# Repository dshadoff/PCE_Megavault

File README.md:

# Multi-Backup Megavault

This is code to run on a 4-megabit Flash memory (SST39SF040), which allows the
save and load of PC Engine backup memory to the flash memory on the cartridge.

The current version allows up to 32 backup memory slots to be saved along with
date infromation and a name/label for the save data.  There is substantially
more space to save information (both data and meta-data), with the possibility
of roughly 100 save areas plus paragraph-length descriptive information (however,
this would require some rethinking of the user interface).

As the NOR Flash is rated for 100 years and 100,000 write cycles, there is no
concern about lifetime under the usage in this application.  The techniques used
in this application can be used for other similar applications as well:
- usage counting
- save data within a cartridge, not relying on CDROM backup memory
- "protection" against usage on unauthorized hardware (check chip identification)

Note that as the special write commands involve specific read/write patterns at
specific addresses, the flash commands cannot be run from the flash memory itself; 
instead, these sepcific sequences have been relocated to execute from user SRAM.

This is prototype software, and as such has been minimally tested.
Use at your own risk.

Also in theis repository is the board layout information for EAGLE, in order
to get these PC board fabricated.

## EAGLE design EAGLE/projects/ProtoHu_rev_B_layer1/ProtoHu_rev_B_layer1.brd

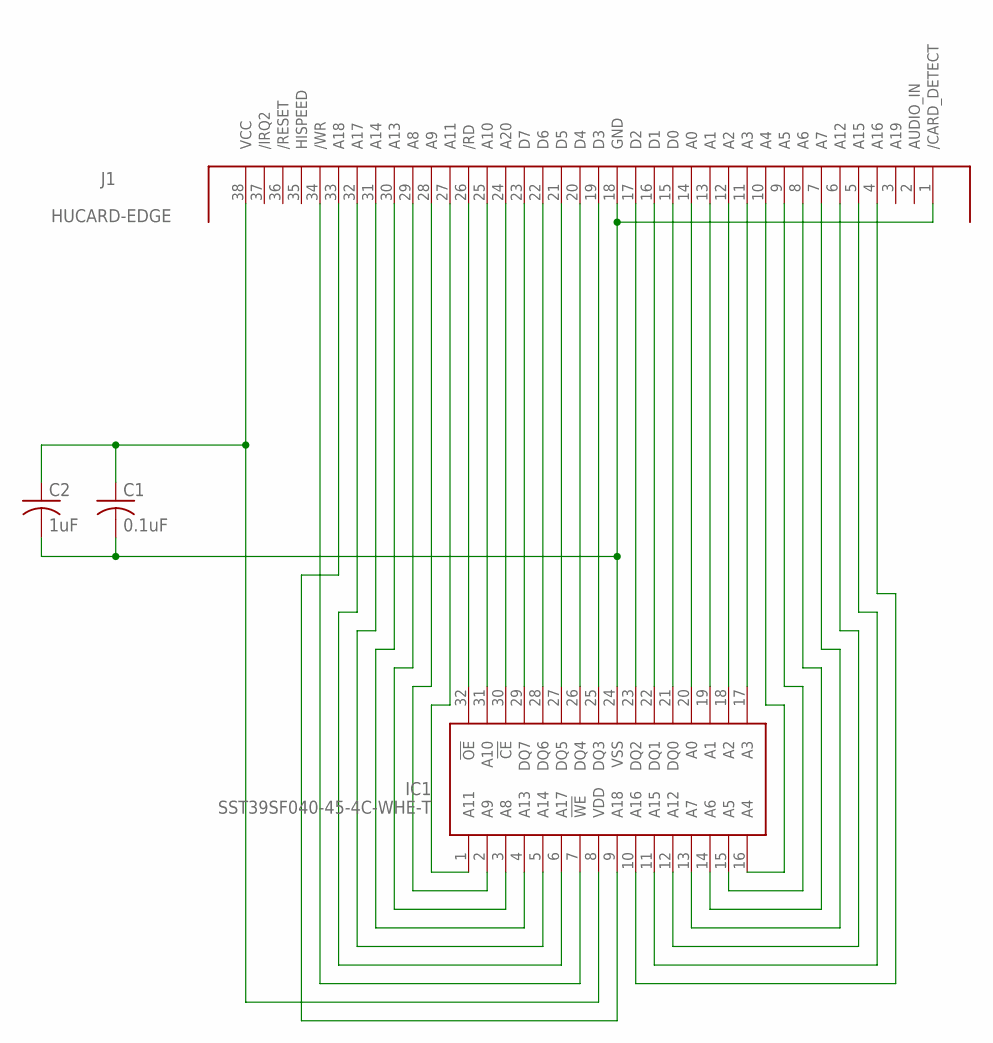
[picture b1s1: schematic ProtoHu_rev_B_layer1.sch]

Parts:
C1: 0.1uF; C0603
C2: 1uF; C0603
IC1: SST39SF040-45-4C-WHE-T; SOP50P1400X120-32N
J1: HUCARD-EDGE

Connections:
GND: C1.2, C2.2, IC1.24 (VSS), J1.1 (/CARD_DETECT), J1.18 (GND)
unnamed: IC1.13 (A7), J1.7 (A7)
unnamed: IC1.12 (A12), J1.6 (A12)
unnamed: IC1.25 (DQ3), J1.19 (D3)
unnamed: IC1.14 (A6), J1.8 (A6)
unnamed: IC1.11 (A15), J1.5 (A15)
unnamed: IC1.10 (A16), J1.4 (A16)
unnamed: IC1.16 (A4), J1.10 (A4)
unnamed: IC1.15 (A5), J1.9 (A5)
unnamed: IC1.17 (A3), J1.11 (A3)
unnamed: IC1.18 (A2), J1.12 (A2)
unnamed: IC1.31 (A10), J1.25 (A10)
unnamed: IC1.32 (!OE), J1.26 (/RD)
unnamed: IC1.1 (A11), J1.27 (A11)
unnamed: IC1.2 (A9), J1.28 (A9)
unnamed: IC1.3 (A8), J1.29 (A8)
unnamed: IC1.19 (A1), J1.13 (A1)
unnamed: IC1.20 (A0), J1.14 (A0)
unnamed: IC1.21 (DQ0), J1.15 (D0)
unnamed: IC1.9 (A18), J1.33 (A18)
unnamed: IC1.7 (!WE), J1.34 (/WR)
unnamed: IC1.22 (DQ1), J1.16 (D1)
unnamed: IC1.6 (A17), J1.32 (A17)
unnamed: IC1.5 (A14), J1.31 (A14)
unnamed: IC1.4 (A13), J1.30 (A13)
unnamed: IC1.23 (DQ2), J1.17 (D2)
unnamed: IC1.30 (!CE), J1.24 (A20)
unnamed: IC1.29 (DQ7), J1.23 (D7)
unnamed: IC1.28 (DQ6), J1.22 (D6)
unnamed: IC1.26 (DQ4), J1.20 (D4)
unnamed: IC1.27 (DQ5), J1.21 (D5)
VCC: C1.1, C2.1, IC1.8 (VDD), J1.38 (VCC)

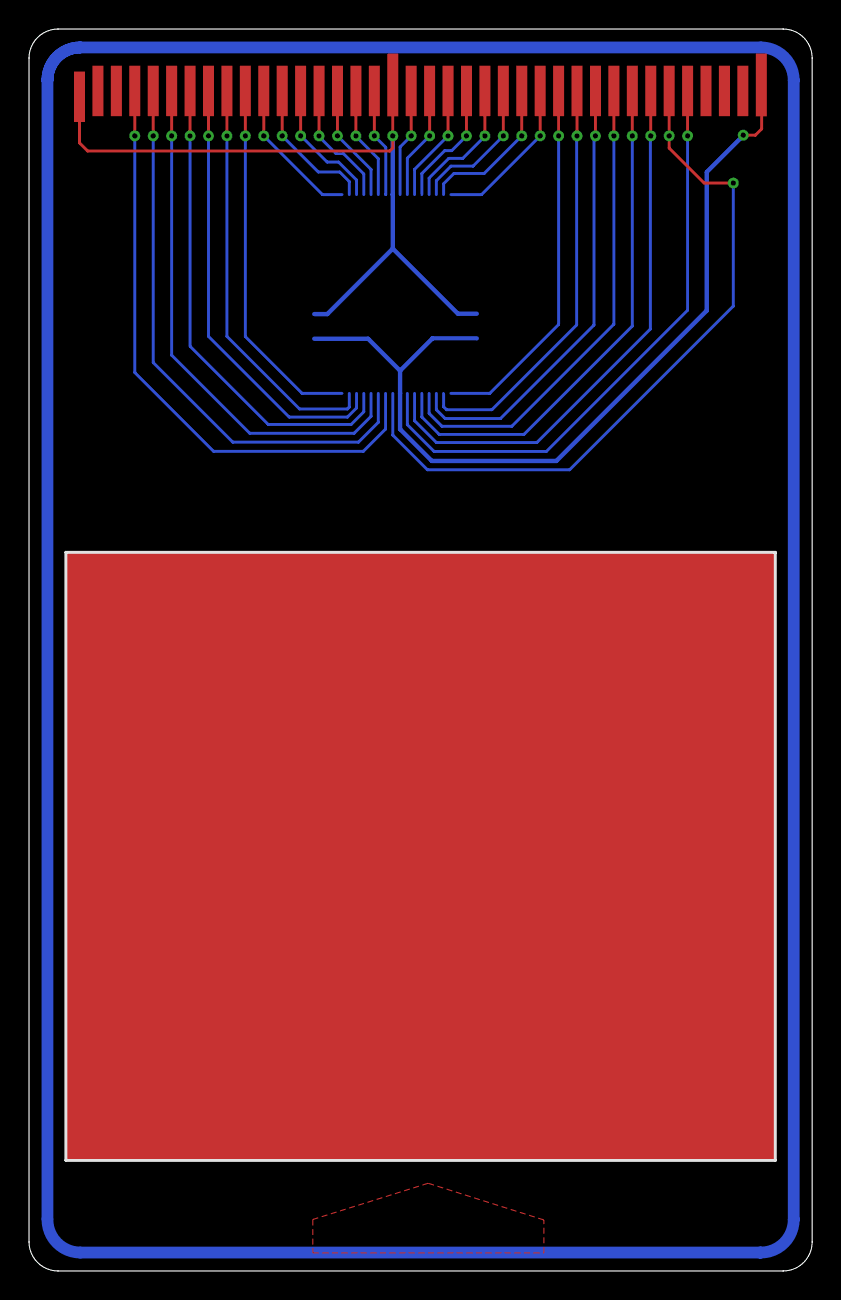
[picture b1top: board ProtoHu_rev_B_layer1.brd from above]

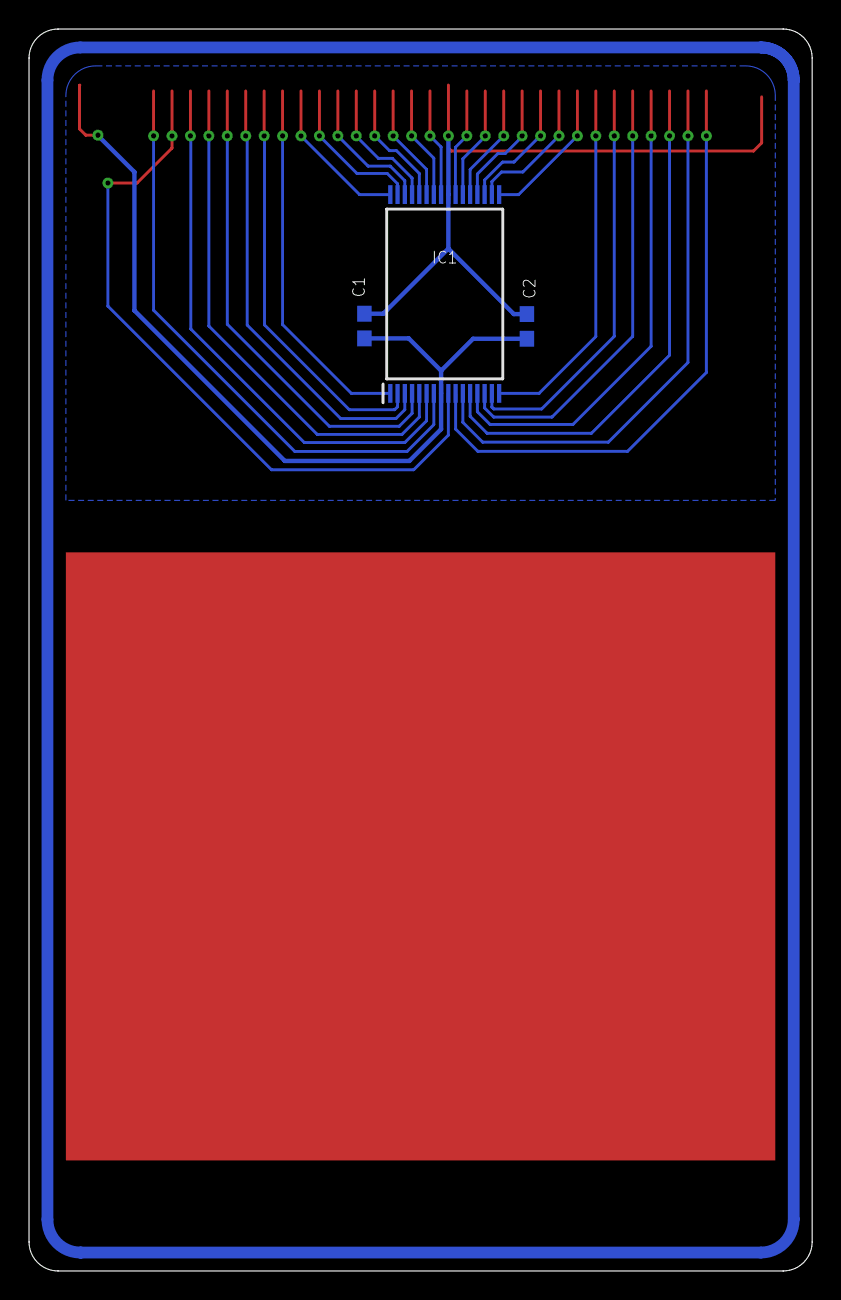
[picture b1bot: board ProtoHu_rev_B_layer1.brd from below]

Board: 2 copper layers, 54.0 x 85.6 mm, 4 parts (3 on the bottom side), 32 nets.

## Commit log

2019-11-18 Add missing steps in BRAM unlock sequence needed only by Tennokoe 2
2019-11-18 Update version/date (re: fix for Tennokoe 2)
2019-11-20 Restructure hierarchy to include PC Board layouts
2019-11-20 Document required HuC library bugfix (just in case)
2020-11-11 Add picture of HuCard
